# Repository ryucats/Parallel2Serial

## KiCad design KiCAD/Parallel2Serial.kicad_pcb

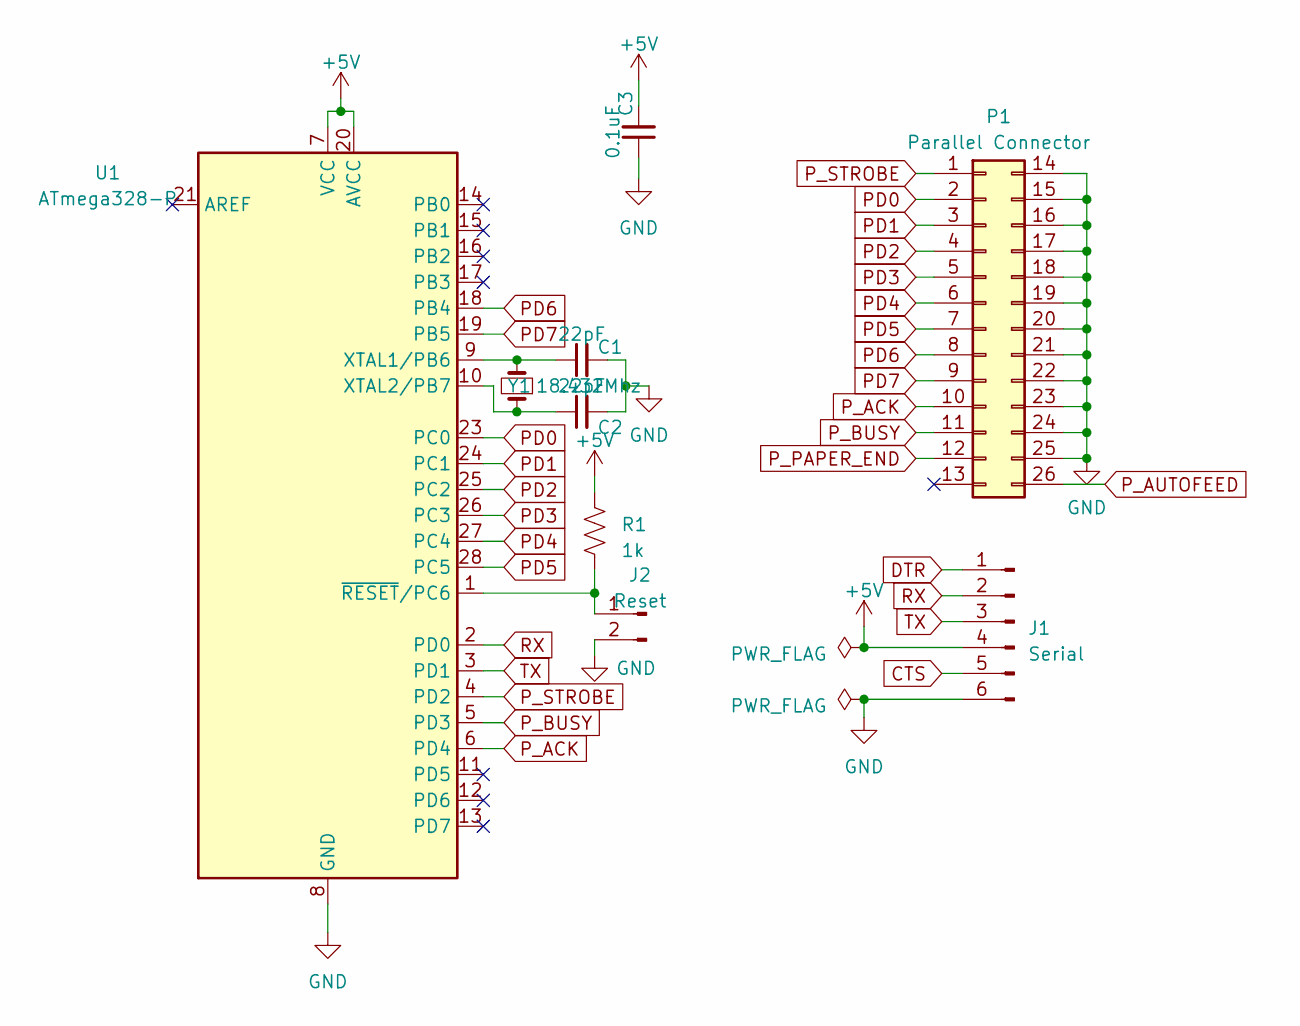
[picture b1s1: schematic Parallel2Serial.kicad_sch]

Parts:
C1, C2: 22pF; C_Disc_D7.5mm_W5.0mm_P5.00mm
C3: 0.1uF; C_Disc_D7.5mm_W5.0mm_P5.00mm
J1: Serial; PinHeader_1x06_P2.54mm_Vertical
J2: Reset; PinHeader_1x02_P2.54mm_Vertical
P1: Parallel Connector
R1: 1k; R_Axial_DIN0207_L6.3mm_D2.5mm_P10.16mm_Horizontal
U1: ATmega328-P; DIP-28_W7.62mm
Y1: 18.432Mhz; Crystal_HC18-U_Vertical

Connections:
+5V: C3.2, J1.4, R1.1, U1.7 (VCC), U1.20 (AVCC)
CTS: J1.5
DTR: J1.1
GND: C1.2, C2.2, C3.1, J1.6, J2.2, P1.14, P1.15, P1.16, P1.17, P1.18, P1.19, P1.20, P1.21, P1.22, P1.23, P1.24, P1.25, U1.8 (GND), U1.22 (GND)
unnamed: J2.1, R1.2, U1.1 (~RESET/PC6)
unnamed: C1.1, U1.9 (XTAL1/PB6), Y1.2
unnamed: C2.1, U1.10 (XTAL2/PB7), Y1.1
PD0: P1.2, U1.23 (PC0)
PD1: P1.3, U1.24 (PC1)
PD2: P1.4, U1.25 (PC2)
PD3: P1.5, U1.26 (PC3)
PD4: P1.6, U1.27 (PC4)
PD5: P1.7, U1.28 (PC5)
PD6: P1.8, U1.18 (PB4)
PD7: P1.9, U1.19 (PB5)
P_ACK: P1.10, U1.6 (PD4)
P_AUTOFEED: P1.26
P_BUSY: P1.11, U1.5 (PD3)
P_PAPER_END: P1.12
P_STROBE: P1.1, U1.4 (PD2)
RX: J1.2, U1.2 (PD0)
TX: J1.3, U1.3 (PD1)

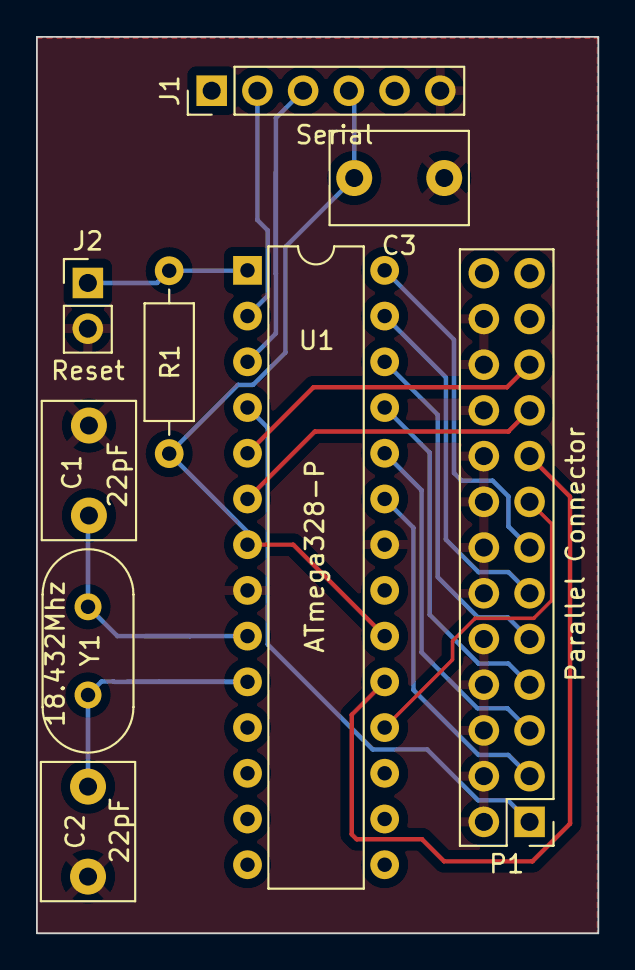
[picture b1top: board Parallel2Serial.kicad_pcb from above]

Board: 2 copper layers, 31.2 x 49.8 mm, 9 parts (0 on the bottom side), 18 nets.

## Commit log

2023-04-08 Initial commit.
